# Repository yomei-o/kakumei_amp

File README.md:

# 革命アンプシリーズ KiCad データ

ヘッドホンアンプ／パワーアンプ（「革命アンプ」シリーズほか）の KiCad プロジェクト一式です。
回路図（`.sch`）、基板（`.kicad_pcb`）、ガーバー／ドリル（`.g*`, `.drl`, `plot/`）、発注用 zip、参考資料 PDF を含みます。

- 作成ツール: KiCad 5 系（`.pro` / `.sch` 形式）
- 各フォルダの `*_mask.kicad_pcb` はマスク付き（基板発注用）レイアウト、`*_.kicad_pcb` は作業用レイアウトです。

## プロジェクト一覧

| フォルダ | 内容 | 主な IC / 素子 |
|---|---|---|
| [`1815_emitter`](1815_emitter) | 2SC1815 エミッタフォロワー ヘッドホンアンプ | 2SC1815 |
| [`386_head_phone2`](386_head_phone2) | NJM386 (LM386) を使ったノイズレスなヘッドホンアンプ | NJM386 / LM386 |
| [`386_kikan`](386_kikan) | LM386 電流負帰還アンプ | LM386 |
| [`lm386_kikan`](lm386_kikan) | LM386 電流負帰還の参考資料（PDF・図のみ） | LM386 |
| [`lm380_kikan`](lm380_kikan) | LM380 を使った電流帰還アンプ | LM380 |
| [`jj47`](jj47) | JJ47 式ヘッドホンアンプ | — |
| [`a47`](a47) | A47 ヘッドホンアンプ | — |
| [`ht82`](ht82) | HT82V739 アンプ | HT82V739 |
| [`njm2073_btl`](njm2073_btl) | NJM2073 BTL アンプ | NJM2073 |
| [`njm_2073_kikan`](njm_2073_kikan) | NJM2073 電流帰還アンプ | NJM2073 |
| [`lm3886_60w`](lm3886_60w) | LM3886 60W パワーアンプ | LM3886 |
| [`SB1-01-MAIN`](SB1-01-MAIN) | SwitchBoard PCB（`switchboard_pcb-ver*.zip` も同系統） | — |

### old/（初期の革命アンプなど）

| フォルダ | 内容 |
|---|---|
| [`old/kakumei_386`](old/kakumei_386) | LM386 革命アンプ |
| [`old/kakumei_380`](old/kakumei_380) | LM380 革命アンプ |
| [`old/kakumei_380_moto`](old/kakumei_380_moto) | LM380 革命アンプ（オリジナル版） |
| [`old/kakumei_380_type2`](old/kakumei_380_type2) | LM380 革命アンプ type2 |
| [`old/kakumei_380_type3`](old/kakumei_380_type3) | LM380 革命アンプ type3 |
| [`old/ayame`](old/ayame) | 工芸アンプ「あやめ」 |
| [`old/kansui_gw`](old/kansui_gw) | kansui_gw |
| [`old/usb_changer`](old/usb_changer) | USB チェンジャー |

### zip/

基板発注用のガーバー zip をまとめたフォルダです（`kakumei_386_005.zip`, `kakumei_380_003.zip` など）。

## 回路図・レイアウト画像

| | |
|---|---|
| 2SC1815 エミッタフォロワー<br> | NJM386 ヘッドホンアンプ<br> |
| JJ47 ヘッドホンアンプ<br> | LM380 電流帰還アンプ<br> |
| HT82V739<br> | NJM2073 BTL<br> |
| NJM2073 電流帰還<br> | LM386 革命アンプ<br> |

## 開き方

1. KiCad 5.x で各フォルダの `.pro` を開きます。
2. 一部のプロジェクトは独自ライブラリ（`*.lib`, `*.dcm`, `*.pretty`）をフォルダ内に同梱しています。
3. 基板を発注する場合は、各フォルダの `plot/` または `*.zip` のガーバーを使ってください。

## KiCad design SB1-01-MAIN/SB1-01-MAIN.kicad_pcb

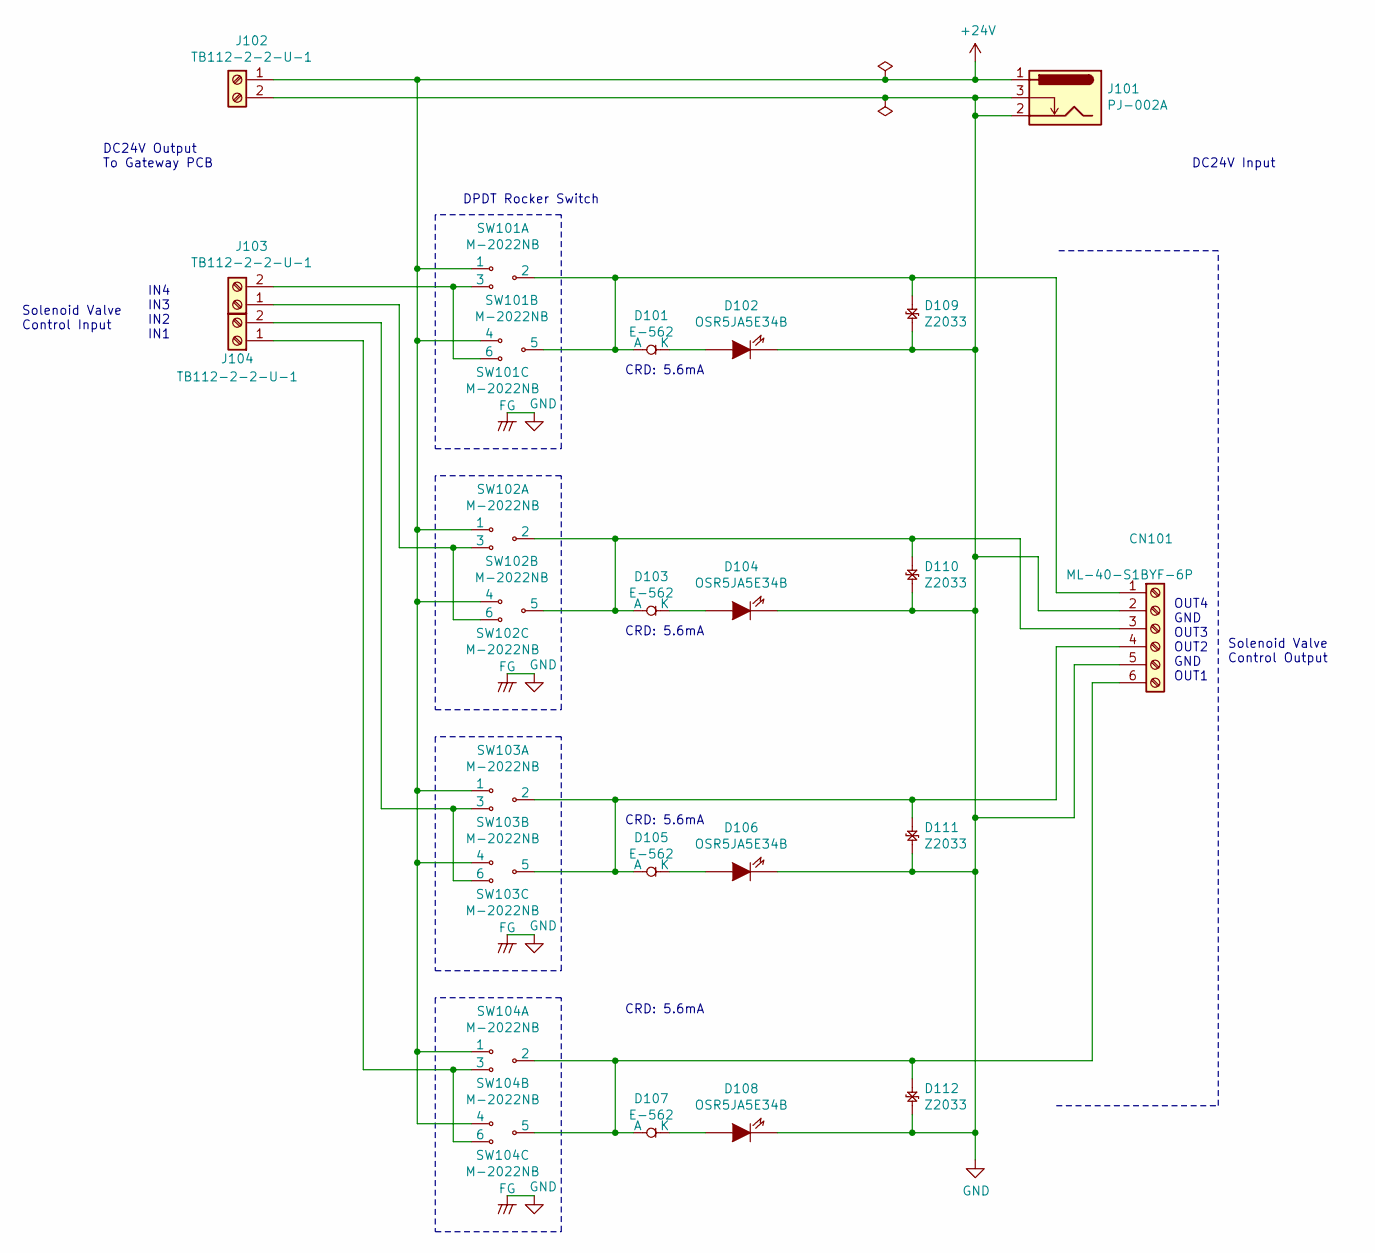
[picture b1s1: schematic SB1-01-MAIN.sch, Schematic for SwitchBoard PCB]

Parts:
CN101: ML-40-S1BYF-6P; ML-40-S1BYF-6P_2; Manufacturer Part Number ML-40-S1BYF-6P
D101, D103, D105, D107: E-562; D_DO-35_SOD27_P7.62mm_Horizontal; Manufacturer Part Number E-562
D102, D104, D106, D108: OSR5JA5E34B; LED_D5.0mm; Manufacturer Part Number OSR5JA5E34B
D109, D110, D111, D112: Z2033; D_DO-15_P10.16mm_Horizontal; Manufacturer Part Number Z2033
J101: PJ-002A; Manufacturer Part Number PJ-002A
J102, J103, J104: TB112-2-2-U-1; TB112-2-2-x-x-x; Manufacturer Part Number TB112-2-2-U-1
SW101, SW102, SW103, SW104: M-2022NB; M-202XN-B; Manufacturer Part Number M-2022NB

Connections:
+24V: J101.1, J102.1, SW101.1, SW101.4, SW102.1, SW102.4, SW103.1, SW103.4, SW104.1, SW104.4
GND: CN101.2, CN101.5, D102.1 (K), D104.1 (K), D106.1 (K), D108.1 (K), D109.2 (A), D110.2 (A), D111.2 (A), D112.2 (A), J101.2, J101.3, J102.2, SW101.FG, SW102.FG, SW103.FG, SW104.FG
unnamed: CN101.1, D101.2 (A), D109.1 (K), SW101.2, SW101.5
unnamed: CN101.3, D103.2 (A), D110.1 (K), SW102.2, SW102.5
unnamed: CN101.4, D105.2 (A), D111.1 (K), SW103.2, SW103.5
unnamed: CN101.6, D107.2 (A), D112.1 (K), SW104.2, SW104.5
unnamed: D101.1 (K), D102.2 (A)
unnamed: D103.1 (K), D104.2 (A)
unnamed: D105.1 (K), D106.2 (A)
unnamed: D107.1 (K), D108.2 (A)
unnamed: J103.1, SW102.3, SW102.6
unnamed: J103.2, SW101.3, SW101.6
unnamed: J104.1, SW104.3, SW104.6
unnamed: J104.2, SW103.3, SW103.6

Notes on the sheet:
DC24V Input
DC24V Output To Gateway PCB
Solenoid Valve Control Input
Solenoid Valve Control Output
DPDT Rocker Switch
CRD: 5.6mA
IN4 IN3 IN2 IN1
OUT4 GND OUT3 OUT2 GND OUT1

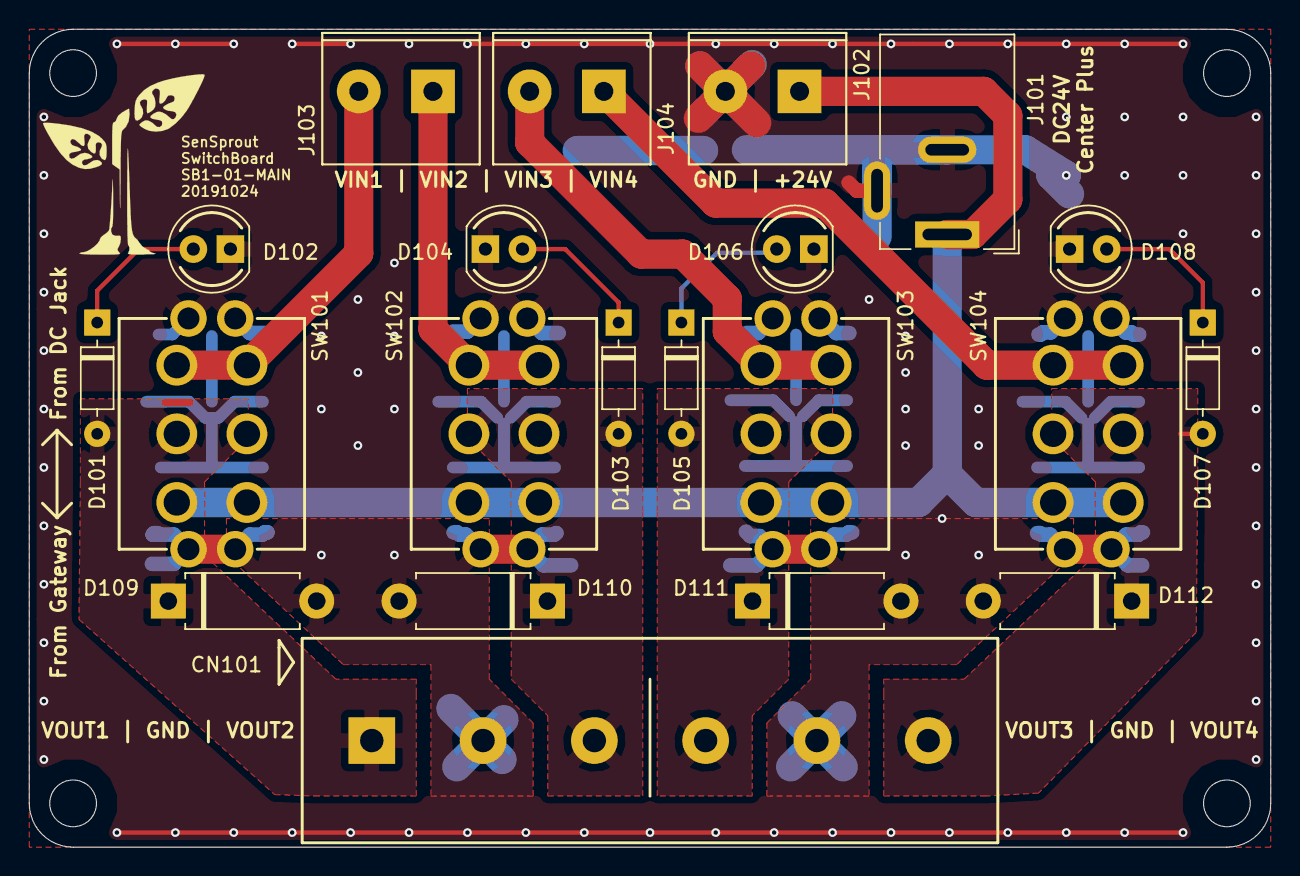
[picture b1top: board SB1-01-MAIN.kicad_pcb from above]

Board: 2 copper layers, 85.0 x 56.0 mm, 25 parts (0 on the bottom side), 14 nets.

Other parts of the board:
%d: NTH_3.2mm
%d#2, %d#3, %d#4: NTH_3.2mm

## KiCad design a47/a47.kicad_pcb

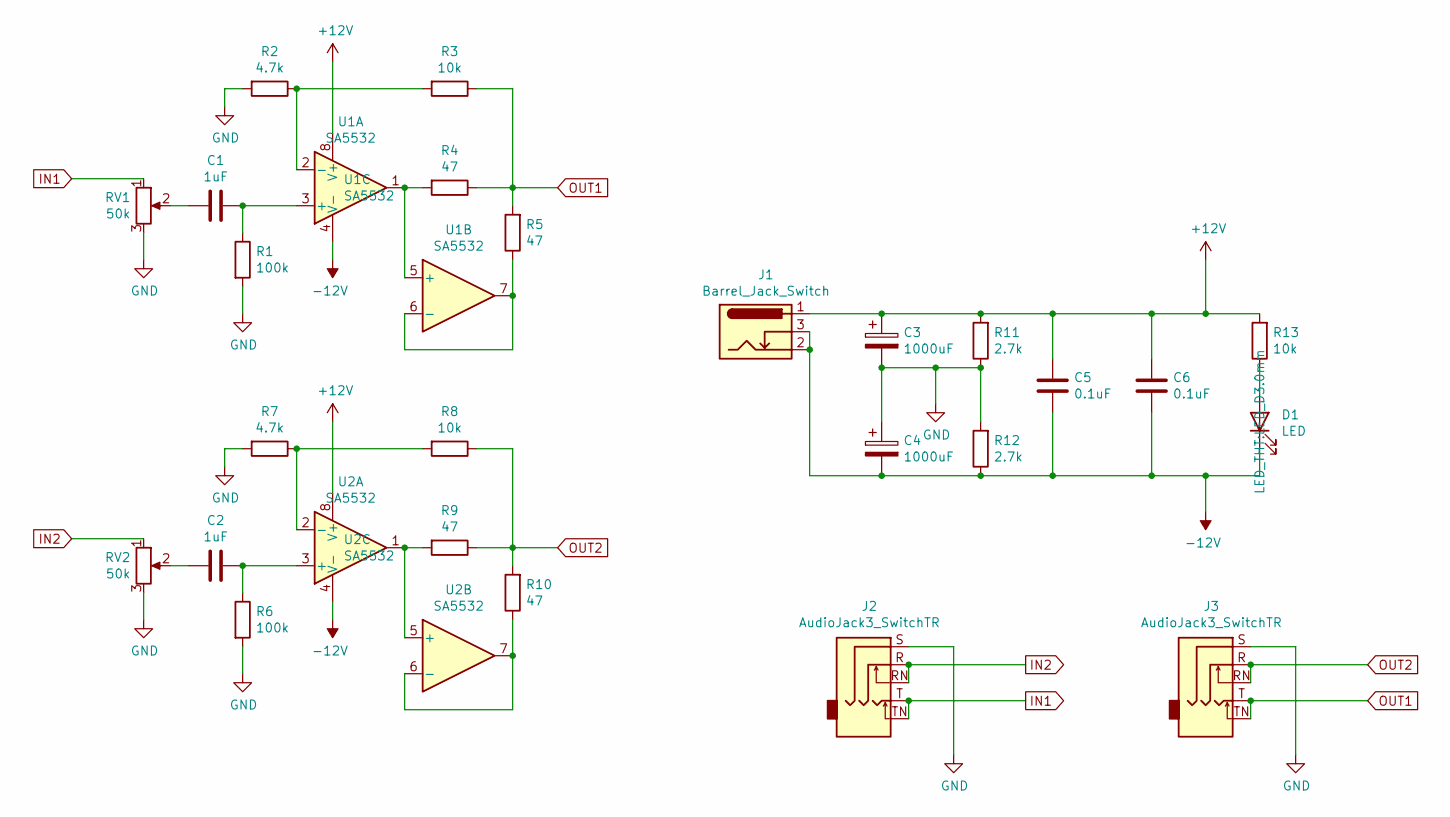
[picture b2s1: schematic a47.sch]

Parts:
C1, C2: 1uF; C_Disc_D10.5mm_W5.0mm_P5.00mm
C3, C4: 1000uF; CP_Radial_Tantal_D10.5mm_P5.00mm
C5, C6: 0.1uF; C_Disc_D7.5mm_W5.0mm_P5.00mm
D1: LED; LED_D3.0mm
J1: Barrel_Jack_Switch; BarrelJack_Horizontal
J2, J3: AudioJack3_SwitchTR; Jack_3.5mm_Ledino_KB3SPRS_Horizontal
R1, R6: 100k; R_Axial_DIN0207_L6.3mm_D2.5mm_P10.16mm_Horizontal
R2, R7: 4.7k; R_Axial_DIN0207_L6.3mm_D2.5mm_P10.16mm_Horizontal
R3, R8, R13: 10k; R_Axial_DIN0207_L6.3mm_D2.5mm_P10.16mm_Horizontal
R4, R5, R9, R10: 47; R_Axial_DIN0207_L6.3mm_D2.5mm_P10.16mm_Horizontal
R11, R12: 2.7k; R_Axial_DIN0207_L6.3mm_D2.5mm_P10.16mm_Horizontal
RV1, RV2: 50k; PinHeader_1x03_P2.54mm_Vertical
U1, U2: SA5532; DIP-8_W7.62mm

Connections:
+12V: C3.1, C5.2, C6.2, J1.1, R11.2, R13.2, U1.8 (V+), U2.8 (V+)
-12V: C4.2, C5.1, C6.1, D1.1 (K), J1.2, J1.3, R12.1, U1.4 (V-), U2.4 (V-)
GND: C3.2, C4.1, J2.S, J3.S, R1.2, R2.2, R6.2, R7.2, R11.1, R12.2, RV1.3, RV2.3
IN1: J2.T, J2.TN, RV1.1
IN2: J2.R, J2.RN, RV2.1
unnamed: C1.1, R1.1, U1.3 (+)
unnamed: C1.2, RV1.2
unnamed: C2.1, R6.1, U2.3 (+)
unnamed: C2.2, RV2.2
unnamed: D1.2 (A), R13.1
unnamed: R2.1, R3.2, U1.2 (-)
unnamed: R4.2, U1.1, U1.5 (+)
unnamed: R5.1, U1.6 (-), U1.7
unnamed: R7.1, R8.2, U2.2 (-)
unnamed: R9.2, U2.1, U2.5 (+)
unnamed: R10.1, U2.6 (-), U2.7
OUT1: J3.T, J3.TN, R3.1, R4.1, R5.2
OUT2: J3.R, J3.RN, R8.1, R9.1, R10.2

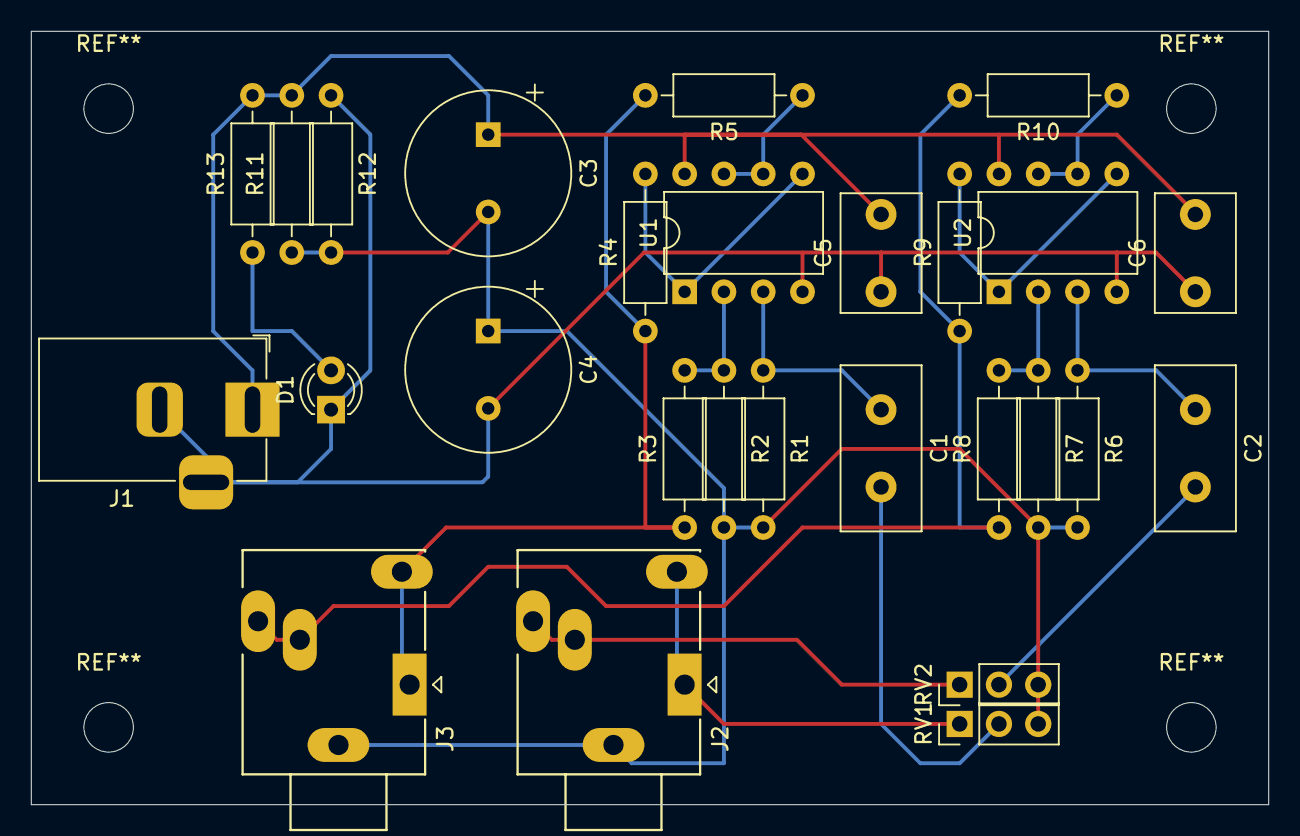
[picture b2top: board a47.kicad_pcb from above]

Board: 2 copper layers, 80.0 x 50.0 mm, 27 parts (0 on the bottom side), 18 nets.

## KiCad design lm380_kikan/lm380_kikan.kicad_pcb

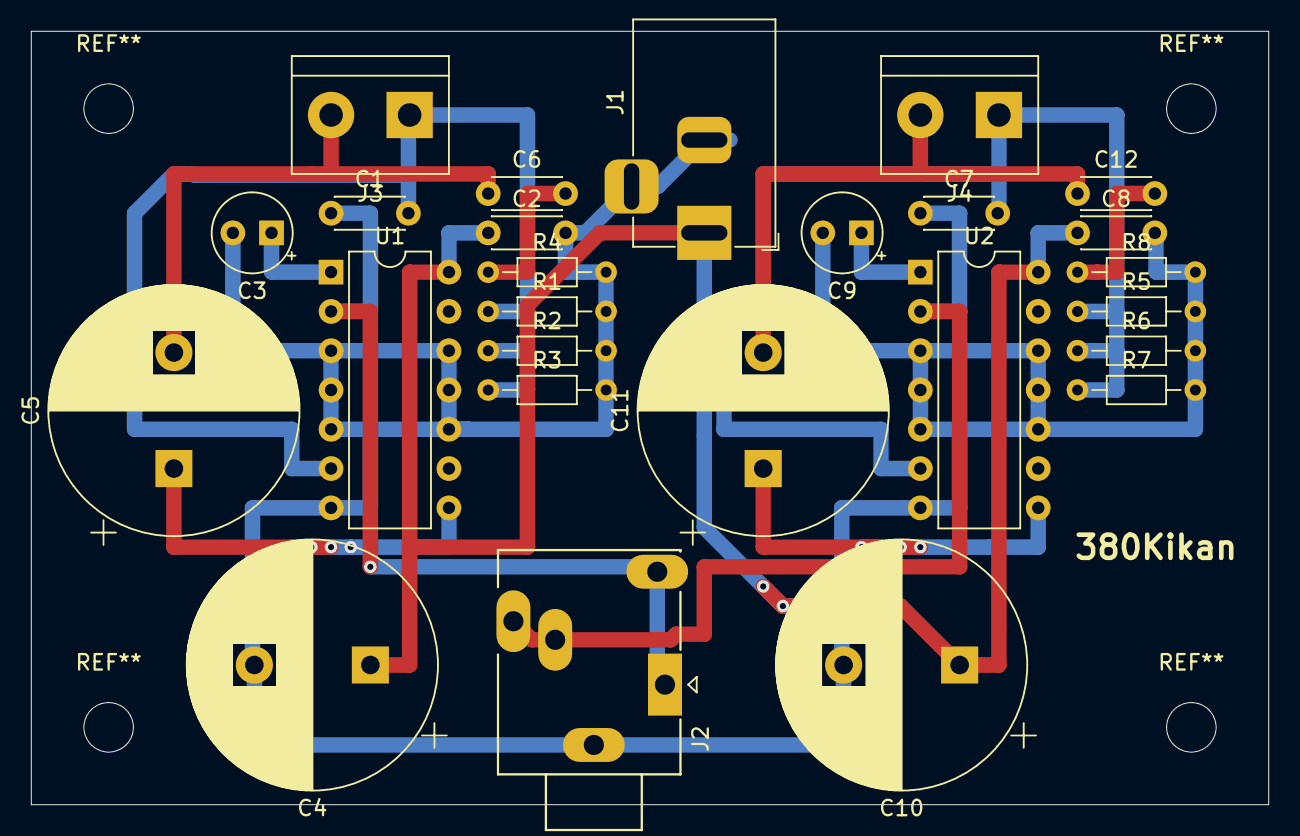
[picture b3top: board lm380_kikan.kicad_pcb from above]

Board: 2 copper layers, 80.0 x 50.0 mm, 26 parts (0 on the bottom side), 14 nets.

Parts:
C1, C7: 2200pf; C_Disc_D4.3mm_W1.9mm_P5.00mm
C2, C6, C8, C12: 0.1uf; C_Disc_D4.3mm_W1.9mm_P5.00mm
C3, C9: 10uf; CP_Radial_Tantal_D5.0mm_P2.50mm
C4, C5, C10, C11: 2200uf; CP_Radial_D16.0mm_P7.50mm
J1: Barrel_Jack_Switch; BarrelJack_Horizontal
J2: AudioJack3_SwitchTR; Jack_3.5mm_Ledino_KB3SPRS_Horizontal
J3, J4: Conn_01x02; TerminalBlock_bornier-2_P5.08mm
R1, R2, R3, R5, R6, R7: 1; R_Axial_DIN0204_L3.6mm_D1.6mm_P7.62mm_Horizontal
R4, R8: 2.2; R_Axial_DIN0204_L3.6mm_D1.6mm_P7.62mm_Horizontal
U1, U2: LM380N; DIP-14_W7.62mm

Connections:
GND: C2.2, C3.2, C4.2, C8.2, C9.2, C10.2, J1.2, J1.3, J2.S, R1.2, R2.2, R3.2, R4.2, R5.2, R6.2, R7.2, R8.2, U1.3, U1.4, U1.5, U1.7, U1.10, U1.11, U1.12, U2.3, U2.4, U2.5, U2.7, U2.10, U2.11, U2.12
IN1: C1.1, J2.T, J2.TN, U1.2
IN2: C7.1, J2.R, J2.RN, U2.2
unnamed: C3.1, U1.1
unnamed: C5.1, U1.8
unnamed: C6.2, R4.1
unnamed: C9.1, U2.1
unnamed: C11.1, U2.8
unnamed: C12.2, R8.1
OUT1: C5.2, C6.1, J3.2
OUT2: C1.2, J3.1, R1.1, R2.1, R3.1, U1.6
OUT3: C11.2, C12.1, J4.2
OUT4: C7.2, J4.1, R5.1, R6.1, R7.1, U2.6
VCC: C2.1, C4.1, C8.1, C10.1, J1.1, U1.14, U2.14

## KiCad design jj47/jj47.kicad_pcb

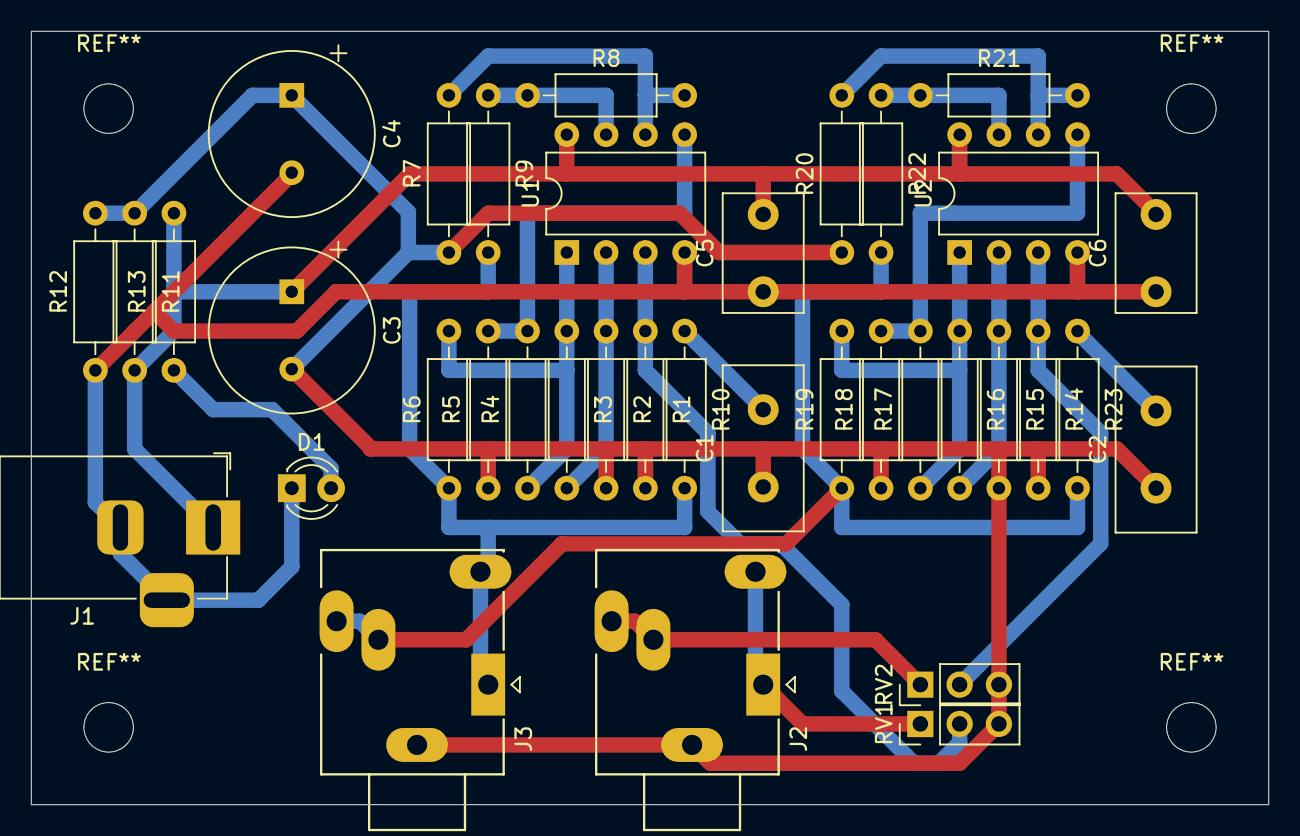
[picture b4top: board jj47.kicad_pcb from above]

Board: 2 copper layers, 80.0 x 50.0 mm, 37 parts (0 on the bottom side), 22 nets.

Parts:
C1, C2: 0.1uF; C_Disc_D10.5mm_W5.0mm_P5.00mm
C3, C4: 1000uF; CP_Radial_Tantal_D10.5mm_P5.00mm
C5, C6: 0.1uF; C_Disc_D7.5mm_W5.0mm_P5.00mm
D1: LED; LED_D3.0mm
J1: Barrel_Jack_Switch; BarrelJack_Horizontal
J2, J3: AudioJack3_SwitchTR; Jack_3.5mm_Ledino_KB3SPRS_Horizontal
R1, R5, R14, R18: 110k; R_Axial_DIN0207_L6.3mm_D2.5mm_P10.16mm_Horizontal
R2, R7, R15, R20: 3.3k; R_Axial_DIN0207_L6.3mm_D2.5mm_P10.16mm_Horizontal
R3, R8, R13, R16, R21: 10k; R_Axial_DIN0207_L6.3mm_D2.5mm_P10.16mm_Horizontal
R4, R17: 330k; R_Axial_DIN0207_L6.3mm_D2.5mm_P10.16mm_Horizontal
R6, R9, R19, R22: 47; R_Axial_DIN0207_L6.3mm_D2.5mm_P10.16mm_Horizontal
R10, R23: 36; R_Axial_DIN0207_L6.3mm_D2.5mm_P10.16mm_Horizontal
R11, R12: 2.7k; R_Axial_DIN0207_L6.3mm_D2.5mm_P10.16mm_Horizontal
RV1, RV2: 10k; PinHeader_1x03_P2.54mm_Vertical
U1, U2: SA5532; DIP-8_W7.62mm

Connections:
+12V: C3.1, C5.2, C6.2, J1.1, R11.2, R13.2, U1.8, U2.8
-12V: C4.2, C5.1, C6.1, D1.1, J1.2, J1.3, R12.1, U1.4, U2.4
GND: C1.1, C2.1, C3.2, C4.1, J2.S, J3.S, R1.2, R2.2, R5.1, R7.1, R11.1, R12.2, R14.2, R15.2, R18.1, R20.1, RV1.3, RV2.3
IN1: J2.T, J2.TN, RV1.1
IN2: J2.R, J2.RN, RV2.1
unnamed: C1.2, R10.1
unnamed: C2.2, R23.1
unnamed: D1.2, R13.1
unnamed: R1.1, RV1.2, U1.3
unnamed: R2.1, R3.2, U1.2
unnamed: R3.1, R4.1, R6.2, U1.1
unnamed: R4.2, R5.2, U1.5
unnamed: R7.2, R8.2, U1.6
unnamed: R8.1, R9.1, U1.7
unnamed: R14.1, RV2.2, U2.3
unnamed: R15.1, R16.2, U2.2
unnamed: R16.1, R17.1, R19.2, U2.1
unnamed: R17.2, R18.2, U2.5
unnamed: R20.2, R21.2, U2.6
unnamed: R21.1, R22.1, U2.7
OUT1: J3.T, J3.TN, R6.1, R9.2, R10.2
OUT2: J3.R, J3.RN, R19.1, R22.2, R23.2

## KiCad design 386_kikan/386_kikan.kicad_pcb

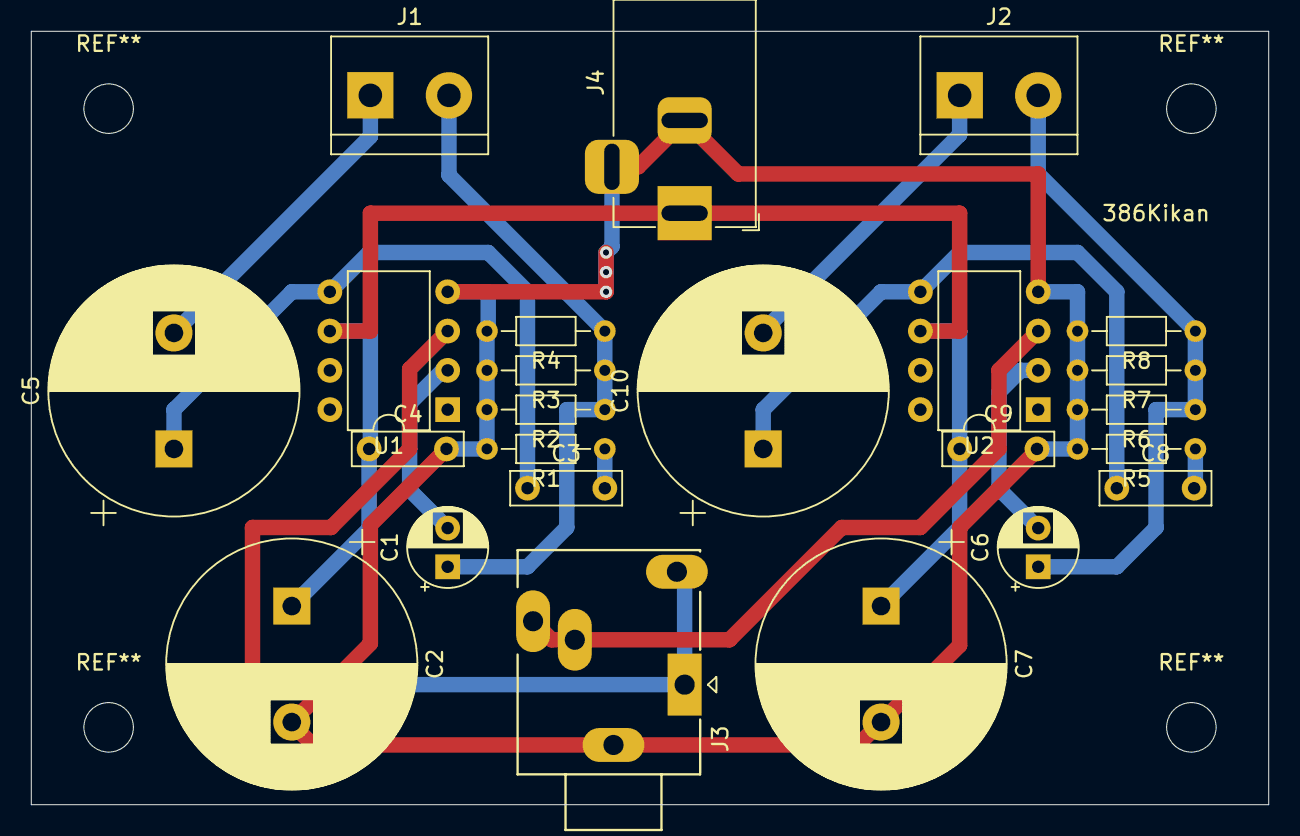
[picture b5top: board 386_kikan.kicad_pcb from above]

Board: 2 copper layers, 80.0 x 50.0 mm, 24 parts (0 on the bottom side), 14 nets.

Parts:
C1, C6: 100uF; CP_Radial_D5.0mm_P2.50mm
C2, C5, C7, C10: 2200uF; CP_Radial_D16.0mm_P7.50mm
C3, C4, C8, C9: 0.1uf; C_Rect_L7.0mm_W2.0mm_P5.00mm
J1, J2: Conn_01x02; TerminalBlock_bornier-2_P5.08mm
J3: AudioJack3_SwitchTR; Jack_3.5mm_Ledino_KB3SPRS_Horizontal
J4: Barrel_Jack_Switch; BarrelJack_Horizontal
R1, R5: 5.1; R_Axial_DIN0204_L3.6mm_D1.6mm_P7.62mm_Horizontal
R2, R3, R4, R6, R7, R8: 1; R_Axial_DIN0204_L3.6mm_D1.6mm_P7.62mm_Horizontal
U1, U2: LM386; DIP-8_W7.62mm

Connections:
GND: C2.2, C4.2, C7.2, C9.2, J3.S, J4.2, J4.3, R1.2, R2.2, R3.2, R4.2, R5.2, R6.2, R7.2, R8.2, U1.4, U2.4
IN1: J3.T, J3.TN, U1.3
IN2: J3.R, J3.RN, U2.3
unnamed: C1.2, U1.2
unnamed: C3.1, C5.1, U1.5
unnamed: C3.2, R1.1
unnamed: C6.2, U2.2
unnamed: C8.2, R5.1
unnamed: C8.1, C10.1, U2.5
OUT1: C5.2, J1.1
OUT2: C1.1, J1.2, R2.1, R3.1, R4.1
OUT3: C10.2, J2.1
OUT4: C6.1, J2.2, R6.1, R7.1, R8.1
VCC: C2.1, C4.1, C7.1, C9.1, J4.1, U1.6, U2.6

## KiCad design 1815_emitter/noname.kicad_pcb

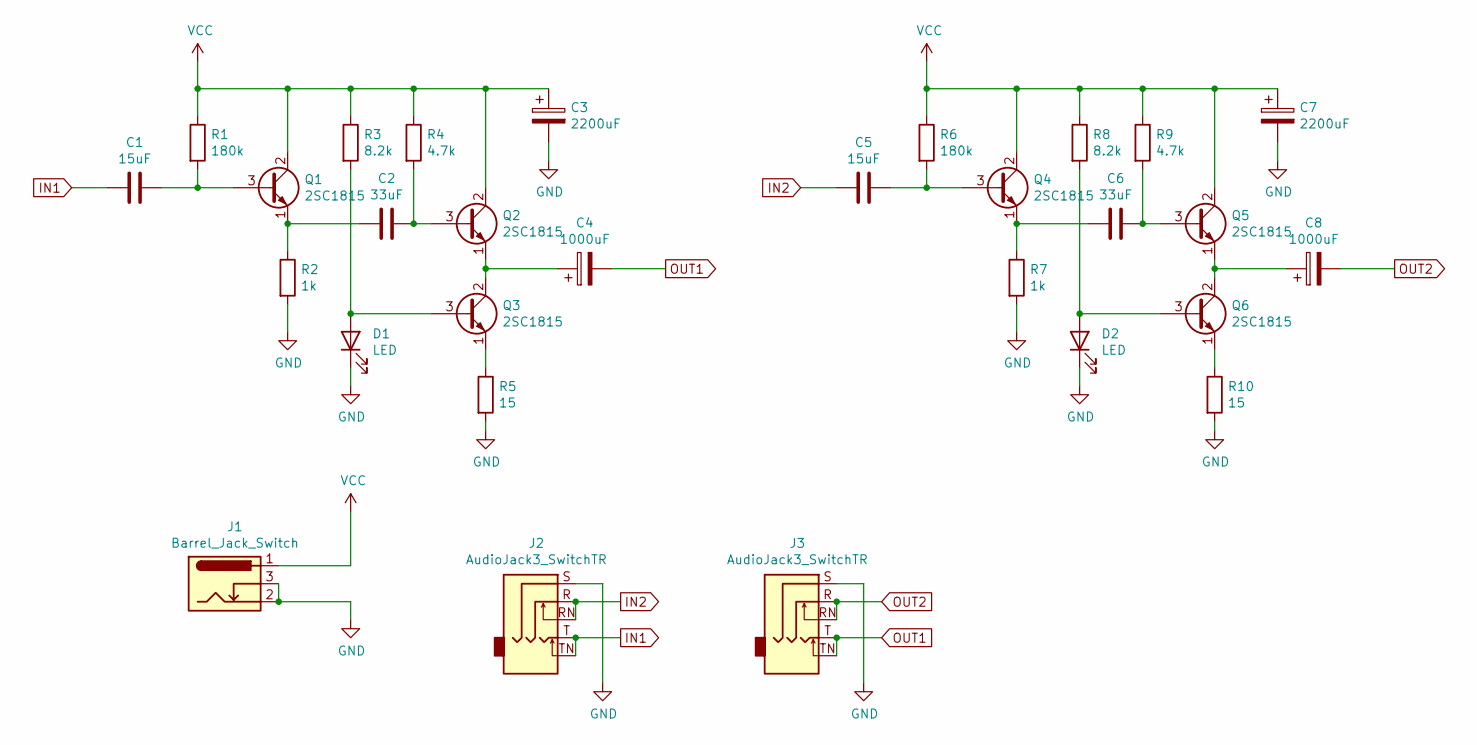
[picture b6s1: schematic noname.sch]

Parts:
C1, C5: 15uF; C_Disc_D5.0mm_W2.5mm_P2.50mm
C2, C6: 33uF; CP_Radial_D8.0mm_P5.00mm
C3, C7: 2200uF; CP_Radial_D10.0mm_P5.00mm
C4, C8: 1000uF; CP_Radial_D10.0mm_P5.00mm
D1, D2: LED; LED_D3.0mm
J1: Barrel_Jack_Switch; BarrelJack_Horizontal
J2, J3: AudioJack3_SwitchTR; Jack_3.5mm_Ledino_KB3SPRS_Horizontal
Q1, Q2, Q3, Q4, Q5, Q6: 2SC1815; TO-92_Inline
R1, R6: 180k; R_Axial_DIN0207_L6.3mm_D2.5mm_P10.16mm_Horizontal
R2, R7: 1k; R_Axial_DIN0207_L6.3mm_D2.5mm_P10.16mm_Horizontal
R3, R8: 8.2k; R_Axial_DIN0207_L6.3mm_D2.5mm_P10.16mm_Horizontal
R4, R9: 4.7k; R_Axial_DIN0207_L6.3mm_D2.5mm_P10.16mm_Horizontal
R5, R10: 15; R_Axial_DIN0207_L6.3mm_D2.5mm_P10.16mm_Horizontal

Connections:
GND: C3.2, C7.2, D1.1 (K), D2.1 (K), J1.2, J1.3, J2.S, J3.S, R2.2, R5.2, R7.2, R10.2
IN1: C1.2, J2.T, J2.TN
IN2: C5.2, J2.R, J2.RN
unnamed: C1.1, Q1.3 (B), R1.2
unnamed: C2.1, Q2.3 (B), R4.2
unnamed: C2.2, Q1.1 (E), R2.1
unnamed: C4.1, Q2.1 (E), Q3.2 (C)
unnamed: C5.1, Q4.3 (B), R6.2
unnamed: C6.1, Q5.3 (B), R9.2
unnamed: C6.2, Q4.1 (E), R7.1
unnamed: C8.1, Q5.1 (E), Q6.2 (C)
unnamed: D1.2 (A), Q3.3 (B), R3.2
unnamed: D2.2 (A), Q6.3 (B), R8.2
unnamed: Q3.1 (E), R5.1
unnamed: Q6.1 (E), R10.1
OUT1: C4.2, J3.T, J3.TN
OUT2: C8.2, J3.R, J3.RN
VCC: C3.1, C7.1, J1.1, Q1.2 (C), Q2.2 (C), Q4.2 (C), Q5.2 (C), R1.1, R3.1, R4.1, R6.1, R8.1, R9.1

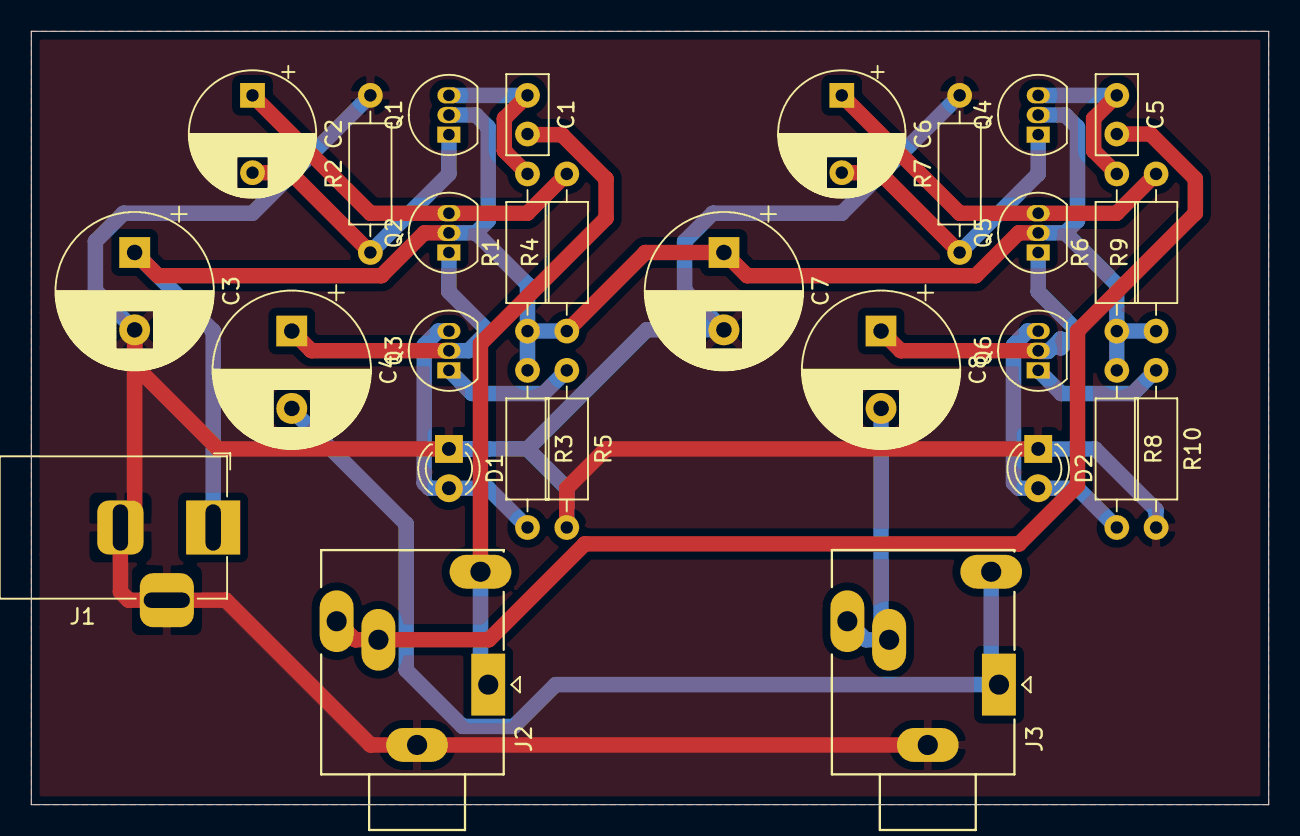
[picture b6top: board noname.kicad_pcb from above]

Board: 2 copper layers, 80.0 x 50.0 mm, 29 parts (0 on the bottom side), 18 nets.

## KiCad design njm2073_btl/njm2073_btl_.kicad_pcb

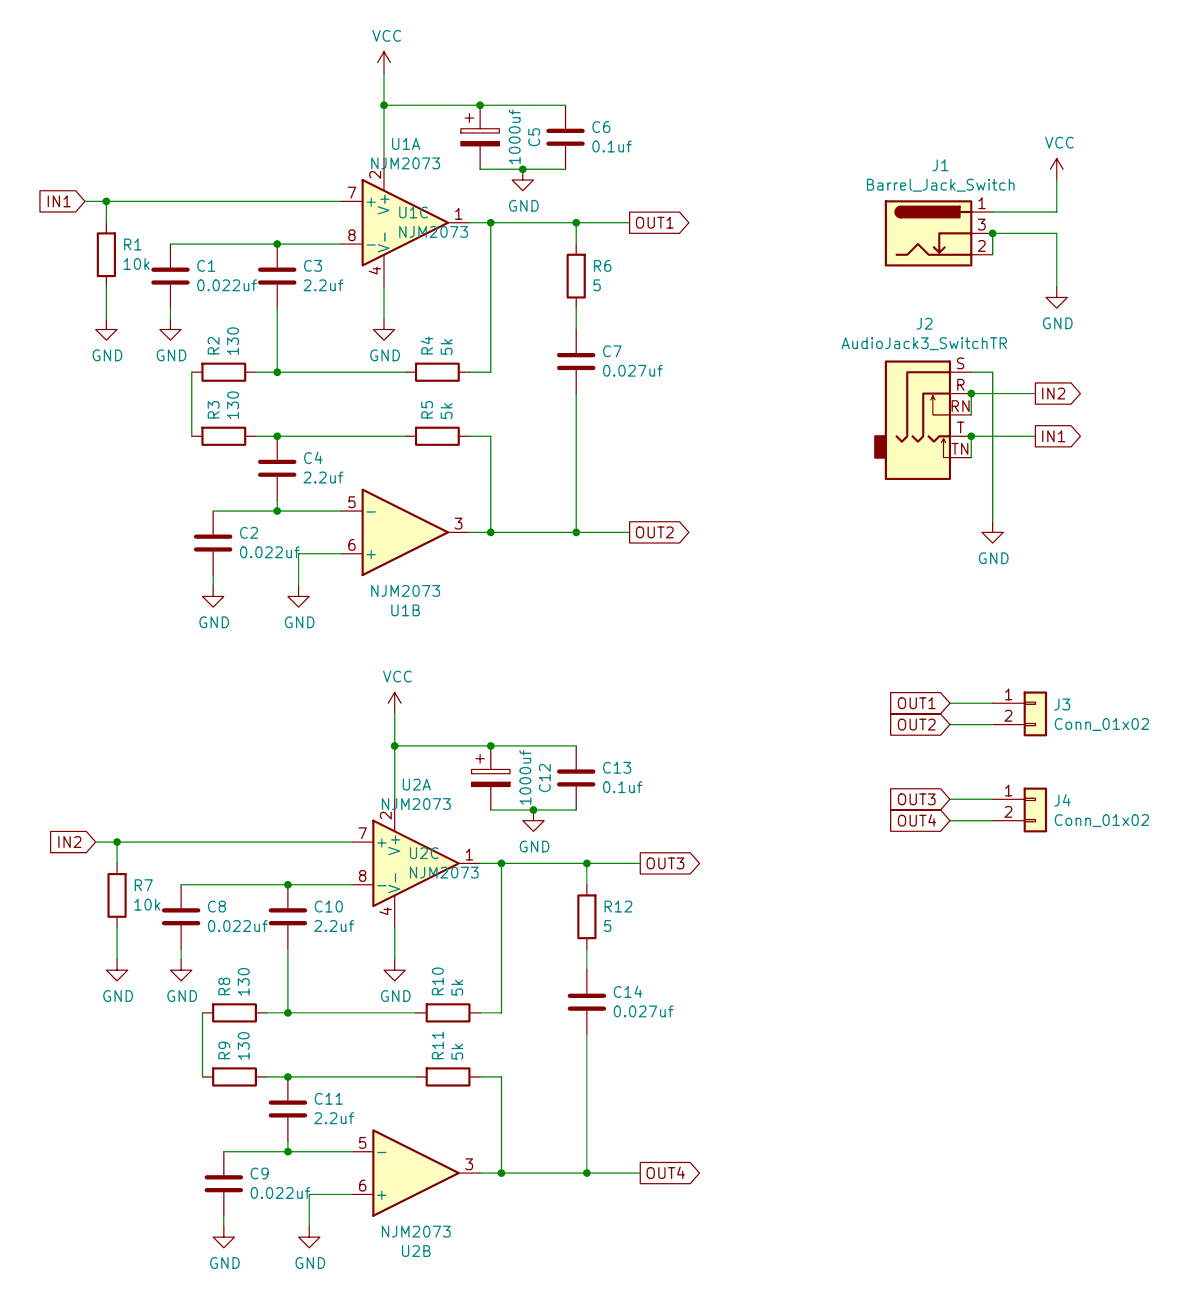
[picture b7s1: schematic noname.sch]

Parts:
C1, C2, C8, C9: 0.022uf; C_Disc_D5.0mm_W2.5mm_P2.50mm
C3, C4, C10, C11: 2.2uf; C_Rect_L10.3mm_W5.0mm_P7.50mm_MKS4
C5, C12: 1000uf; CP_Radial_D10.0mm_P5.00mm
C6, C13: 0.1uf; C_Rect_L7.0mm_W2.0mm_P5.00mm
C7, C14: 0.027uf; C_Rect_L7.0mm_W2.0mm_P5.00mm
J1: Barrel_Jack_Switch; BarrelJack_Horizontal
J2: AudioJack3_SwitchTR; Jack_3.5mm_Ledino_KB3SPRS_Horizontal
J3, J4: Conn_01x02; TerminalBlock_bornier-2_P5.08mm
R1, R7: 10k; R_Axial_DIN0204_L3.6mm_D1.6mm_P7.62mm_Horizontal
R2, R3, R8, R9: 130; R_Axial_DIN0204_L3.6mm_D1.6mm_P7.62mm_Horizontal
R4, R5, R10, R11: 5k; R_Axial_DIN0204_L3.6mm_D1.6mm_P7.62mm_Horizontal
R6, R12: 5; R_Axial_DIN0204_L3.6mm_D1.6mm_P7.62mm_Horizontal
U1, U2: NJM2073; DIP-8_W7.62mm

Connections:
GND: C1.2, C2.2, C5.2, C6.2, C8.2, C9.2, C12.2, C13.2, J1.2, J1.3, J2.S, R1.1, R7.1, U1.4 (V-), U1.6 (+), U2.4 (V-), U2.6 (+)
IN1: J2.T, J2.TN, R1.2, U1.7 (+)
IN2: J2.R, J2.RN, R7.2, U2.7 (+)
unnamed: C1.1, C3.1, U1.8 (-)
unnamed: C2.1, C4.2, U1.5 (-)
unnamed: C3.2, R2.1, R4.2
unnamed: C4.1, R3.1, R5.2
unnamed: C7.1, R6.1
unnamed: C8.1, C10.1, U2.8 (-)
unnamed: C10.2, R8.1, R10.2
unnamed: C11.1, R9.1, R11.2
unnamed: C9.1, C11.2, U2.5 (-)
unnamed: C14.1, R12.1
unnamed: R2.2, R3.2
unnamed: R8.2, R9.2
OUT1: J3.1, R4.1, R6.2, U1.1
OUT2: C7.2, J3.2, R5.1, U1.3
OUT3: J4.1, R10.1, R12.2, U2.1
OUT4: C14.2, J4.2, R11.1, U2.3
VCC: C5.1, C6.1, C12.1, C13.1, J1.1, U1.2 (V+), U2.2 (V+)

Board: 2 copper layers, 32 parts (0 on the bottom side), 20 nets, no tracks yet.
